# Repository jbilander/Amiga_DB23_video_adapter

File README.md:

# Amiga DB23 Video Adapter

## Overview

The Amiga DB23 Video Adapter is a small plug-mounted PCB that fits directly onto the Amiga's 
DB23 video port. It is primarily used to build Amiga video cables — either a SCART (RGBS) or 
VGA (RGBHV) cable — while also buffering and filtering the Amiga's analog video signals for 
use with modern displays. Optionally, it allows switching between true PAL and NTSC clock 
frequencies without rebooting or using software.

***

***

<br />

***

### Video Signal Conditioning (Rev 1B)

- **HSync and VSync** are passed through a dual non-inverting Schmitt-trigger buffer (U1) to 
  reduce jitter and noise on the sync lines.
- **RGB signals** are routed through a THS7374 4-channel video amplifier (U3) with its 
  low-pass filter enabled. This effectively removes the horizontal banding and "jailbar" 
  interference patterns commonly seen when connecting an Amiga's 15 kHz signal to LCD displays.
  > ⚠️ A 15 kHz-capable display is required. See [15khz.wikidot.com](http://15khz.wikidot.com/) 
  > for compatible monitors.

### PAL/NTSC Clock Switching (Optional)

When a crystal oscillator (Y1) is populated, the adapter can supply an external pixel clock 
to the Amiga's Agnus/Alice chip, allowing the machine to be switched between PAL and NTSC 
video modes. The slide switch (SW1) enables or disables the `/XCLKEN` signal — when asserted, 
this tells Agnus/Alice to use the external clock from the adapter instead of the onboard 
motherboard oscillator.

The switch itself is hardware-debounced using a resistor-capacitor (RC) circuit combined with 
the hysteresis of a dual-inverting Schmitt-trigger IC (U2), ensuring clean, glitch-free 
switching.

Two solder pads (`XCLKEN` and `/XCLKEN`) are provided on the PCB. An optional jumper wire 
can be soldered from one of these pads back to pin 41 of a switchable Agnus chip 
(or JP4 on the A500 Rev. 6A board), so that the switch on the adapter controls both the 
external clock enable and the Agnus clock selection simultaneously.

> ⚠️ **Before attempting this mod**, verify that your Agnus revision supports hardware 
> PAL/NTSC switching, and confirm that JP4 is not already bridged to GND. 
> All ECS Agnus chips can be switched in **software** if the hardware pin is not available — 
> use the Early Startup Menu (hold both mouse buttons at reset) on KS 3.0+, or a tool 
> such as [Degrader](https://aminet.net/package/util/boot/Degrader).

#### Choosing the correct crystal and solder pad

Install a crystal **opposite** to the one already on your Amiga's motherboard:

| Motherboard oscillator | Install crystal | Solder jumper wire to pad |
|------------------------|-----------------|---------------------------|
| PAL (28.37516 MHz)     | NTSC (28.63636 MHz) | `XCLKEN` |
| NTSC (28.63636 MHz)    | PAL (28.37516 MHz)  | `/XCLKEN` |

> The jumper wire is entirely optional. Without it you can still enable/disable the external 
> clock via SW1, and switch the Agnus video mode independently through software or the 
> Early Startup Menu.

---

## Why use this adapter with XCLK?

You don't have to — but being able to switch between true native PAL and true native NTSC on 
the same machine is a very compelling feature. It gives you:

- ✅ Correct **aspect ratio** for game graphics designed for a specific video standard
- ✅ Correct **sound playback speed** (PAL/NTSC run at different clock rates)
- ✅ Correct **gameplay speed** and smooth scrolling in both PAL 50 Hz and NTSC 60 Hz

For example, compare the screenshots below from *Defender of the Crown*, with its stunning 
artwork by artist **Jim Sachs**. The game was designed for NTSC and looks significantly better 
in NTSC mode (bottom row) — in PAL mode (top row) everything appears vertically squashed.

<br />

**PAL (top) vs NTSC (bottom):**

***

## Usage Scenarios

### 1 — Amiga DB23 to SCART (RGBS)
Build a cable carrying RGB + Composite Sync (CSync) to a SCART-equipped display.  
U1 and C3 are **not required** in this configuration.  
Y1 can optionally be populated for PAL/NTSC switching as described above.

### 2 — Amiga DB23 to VGA (RGBHV)
Build a cable carrying RGB + separate HSync/VSync to a VGA monitor.  
Requires a [15 kHz-compatible monitor](http://15khz.wikidot.com/).  
U1 and C3 **are required** in this configuration.  
Y1 can optionally be populated for PAL/NTSC switching as described above.

### 3 — Plug only, no cable (clock switching only)
Populate Y1 and the XCLK circuitry, but attach no output cable. Useful if you are already 
using an RGBtoHDMI or similar device for display output but want to retain hardware 
PAL/NTSC switching via the adapter's switch.

***

## Bill of Materials (Rev 1B and 1C)

**J1, U3 and RN1 are required for both SCART and VGA builds.**

| Reference | Qty | Value | Description | Package | Mouser / Notes |
|-----------|-----|-------|-------------|---------|----------------|
| J1 | 1 | DB23 Female | DB-23 female connector (Amiga video port) | DB-23 | [Aliexpress DB23 Female](https://www.aliexpress.com/item/1005004634222021.html) |
| U1 | 1 | 74HCT2G17 | Dual non-inverting Schmitt-trigger buffer — **VGA only** | TSOP-6 | [771-HCT2G17GV125](https://www.mouser.com/ProductDetail/771-HCT2G17GV125) |
| U2 | 1 | 74HCT2G14 | Dual inverting Schmitt-trigger buffer (SW1 debounce) — **XCLK optional** | TSOP-6 | [771-HCT2G14GV125](https://www.mouser.com/ProductDetail/771-HCT2G14GV125) |
| U3 | 1 | THS7374IPWR | 4-channel video amplifier with low-pass filter | TSSOP-14 | [595-THS7374IPWR](https://www.mouser.com/ProductDetail/595-THS7374IPWR) |
| U4 | 1 | 74LVC1GX04 | Crystal clock buffer — **XCLK optional** | TSOP-6 | [771-LVC1GX04GV125](https://www.mouser.com/ProductDetail/771-LVC1GX04GV125) |
| Y1 | 1 | 28.37516 MHz (PAL) or 28.63636 MHz (NTSC) | Crystal oscillator, CL=16pF — **XCLK optional** | 3.2 x 2.5 mm | e.g. ABM8-28.375MHZ-B2-T (PAL) or ECS-286.3-18-33-JEM-TR (NTSC) |
| RN1 | 1 | 75Ω | Resistor network, 4× 75Ω isolated (CAT16-75R0F4LF) | 1206 | [CAT16-75R0F4LF](https://www.mouser.com/ProductDetail/652-CAT16-75R0F4LF) |
| SW1 | 1 | SW_SPDT | Slide switch, enables/disables `/XCLKEN` (external clock to Agnus/Alice). Recommended: SS12D00 3-pin 1P2T, pin pitch 2.5 mm, handle length 5 mm — **XCLK optional** | | e.g. [AliExpress SS12D00](https://www.aliexpress.com/item/1005008330569768.html) |
| R1 | 1 | 100Ω | **Optional** — CCK clock termination. Populate only if experiencing clock interference noise. See [vidmod fix](http://www.l8r.net/technical/wblock/a4000hard/vidmod.html) | 1206 | |
| R2 | 1 | 75Ω | RGB mode autoselect — **SCART only** (drives SCART pin 16 high for RGB mode) | 1206 | |
| R3 | 1 | 1kΩ | AV mode autoselect — **SCART only** (drives SCART pin 8 high at 9.5–12V so TV automatically switches to SCART input) | 1206 | |
| R4 | 1 | 150Ω | Damping resistor XCLK-line — **XCLK optional** | 1206 | |
| R5 | 1 | 330Ω | CSync resistor — **SCART only** | 0805 | |
| R6, R7, R8 | 3 | 75Ω | Video termination resistor | 0603 | |
| R9, R10 | 2 | 10kΩ | Resistor (SW1 RC debounce) — **XCLK optional** | 0805 | |
| R11 | 1 | 1kΩ | Resistor — **XCLK optional** | 0603 | |
| R12 | 1 | 2.2MΩ | Resistor — **XCLK optional** | 0603 | |
| C1, C2 | 2 | 100nF | Decoupling capacitor | 0805 | (C2 is for SW1 RC debounce)|
| C3 | 1 | 100nF | Decoupling capacitor — **VGA only** | 0603 | |
| C4, C5 | 2 | 100nF | Decoupling capacitor — **XCLK optional** | 0603 | |
| C6, C7 | 2 | 32pF | Crystal load capacitor (06031A320FAT2A) — **XCLK optional** | 0603 | [581-06031A320FAT2A](https://www.mouser.com/ProductDetail/581-06031A320FAT2A) |

### Partial BOM by build type

| Component | Mandatory (both) | SCART only | VGA only | XCLK optional |
|-----------|:---:|:---:|:---:|:---:|
| J1, U3, RN1 | ✅ | | | |
| C1, R6, R7, R8 | ✅ | | | |
| R2, R3, R5 | | ✅ | | |
| U1, C3 | | | ✅ | |
| U2, U4, Y1, SW1 | | | | ✅ |
| C2, C4, C5, C6, C7 | | | | ✅ |
| R4, R9, R10, R11, R12 | | | | ✅ |
| R1 | optional | | | |

### SCART cable wiring reference

| Signal | Resistor | Value | SCART pin | Notes |
|--------|----------|-------|-----------|-------|
| CSync  | R5 | 330Ω | Pin 20 | Composite sync / composite video in, 1V incl. sync |
| +5V    | R2 | 75Ω  | Pin 16 | RGB select: High (1–3V) = RGB mode, Low (0–0.4V) = Composite |
| +12V   | R3 | 1kΩ  | Pin 8  | AV autoswitch: High (9.5–12V) = AV mode, Low (0–2V) = TV mode |

### VGA cable reference

U1 (74HCT2G17) buffers HSync and VSync. Datasheet: [74HC/HCT2G17](https://assets.nexperia.com/documents/data-sheet/74HC_HCT2G17.pdf)

---

## How to build Rev 1B

The following step-by-step guide documents a VGA (RGBHV) cable build using a cheap 
thin VGA cable as the source, which works very well since these cables already contain 
individually shielded wires inside.

### Step 1 — Prepare the DB23 connector

Start by gently prying the solder lug pins outward slightly on the DB23 connector so 
that they can wrap around the standard 1.6 mm PCB thickness. The back of a pair of 
tweezers works well for this — just enough to open them up without bending them too far.

### Step 2 — Fit the PCB into the connector

Carefully sandwich the PCB between the solder cups of the connector, making sure the 
alignment is correct. The fit is very tight — press the PCB in by hand as far as it 
will go. At this stage there will still be a small gap visible between the blue plastic 
back of the connector and the PCB edge; this is expected.

### Step 3 — Press the PCB fully home in a vise

Place the PCB and connector assembly into a bench vise as shown, then slowly tighten 
the vise to press the PCB all the way flush against the plastic back of the connector.

### Step 4 — Test fit in the plastic shell

Test that the assembly fits inside the plastic shell and clears the screw terminal posts.

> **Note on shell compatibility:**
> - **Older DB23 shells** have approximately 21.5 mm clearance between the screw terminal 
>   posts — Rev 1B (20.6 mm wide) fits these without any modification.
> - **Newer shells** (available from [AliExpress](https://www.aliexpress.com/item/1005004634222021.html)) 
>   have only 20 mm spacing, which means Rev 1B overlaps the posts by about 0.6 mm and 
>   the two shell halves will not close without a slight carve or filing of the plastic posts.
> - **Rev 1C** has been narrowed to 19.8 mm and fits the new shells without any modification. 
>   Rev 1B and Rev 1C are otherwise electrically identical — the BOM and schematic are the same.

In pic9, the right side shows a fully soldered connector test-fitted in an older shell 
where it clears the posts cleanly. On the left you can see a bare PCB test-fitted in the 
newer style shell, where the slight overlap on the posts is visible.

Once you have confirmed the fit, solder all the connector solder cups on both sides of 
the PCB and connector.

### Step 5 — Solder the SMD components

With the connector soldered, proceed to populate and solder the SMD components on the 
PCB. If you are fitting the optional crystal oscillator (Y1) for XCLK switching, it is 
recommended to reflow it first with a hot air rework station before populating nearby 
smaller components that could otherwise be displaced by the airflow. All other SMD 
components can be soldered with a regular soldering iron.

Leave the through-hole slide switch (SW1) until last — it is easier to solder everything 
else first without the switch body in the way.

> **Tip on cable shielding:** It is good practice to solder the cable's outer shielding 
> braid to the DB23 connector's metal shell. The Amiga's DB23 shell is connected to GND 
> on the motherboard, so having the shield connected here means GND will make contact 
> first if the cable is ever hot-plugged, protecting the circuitry. A high-powered 
> soldering iron or desoldering gun (such as the ZD-915) with sufficient thermal mass 
> is recommended for this step. Pre-crimping a Dupont male pin onto the bundled shielding 
> wire makes it easier to tin and solder to the shell.

### Step 6 — Modify the shell for the cable strain relief

To fit the metal cable strain relief inside the shell, the two small inner plastic walls 
nearest the cable exit hole need to be removed — they are the ones that interfere with 
the strain relief clamp. Use a pair of electronics pliers or flush cutters to snip them 
off as close to the side wall and floor of the shell as possible. Be careful to only 
remove the two pieces immediately next to the exit hole, not the similar supports further 
inside that the PCB rests on.

### Step 7 — Modify the strain relief to fit

The standard metal cable strain relief may need a small amount of filing to fit 
comfortably inside the shell. The standard M3 screws supplied with the strain relief 
may also need to be swapped for M3 screws with a lower-profile head. Once modified, 
the strain relief fits neatly wedged between the back edge of the PCB and the rear 
wall of the shell. Alternatively, a custom strain relief could be 3D printed in plastic 
to avoid the need for any hand filing.

### Step 8 — Drill the switch hole

One half of the plastic shell needs a hole drilled for the SW1 switch handle to protrude 
through. Mark the centre point with a sharp tweezer or scribe — it sits midway between 
the two screw holes, and midway between the recessed label area and the thumb-grip 
grooves on the shell.

Start with a 1 mm drill bit turned carefully by hand to establish a centred pilot hole, 
then step up through 2 mm, 4 mm, and finally 6 mm using a power drill. A 6 mm diameter 
hole gives the switch handle enough room to travel freely between both positions without 
touching the sides.

### Step 9 — Test fit the switch

Test fit the shell halves and confirm that the switch handle protrudes a few millimetres 
through the hole and can be toggled comfortably between both positions by hand.

### Step 10 — Solder the cable wires

Solder the cable wires to the solder pads on the PCB:

- **Underside (pic14):** All GND wires are soldered here. In this VGA build the 5V and 
  12V pads are unused.
- **Front side (pic15):** The analogue Red, Green and Blue signal wires are soldered to 
  their respective pads, along with HSync (grey wire) and VSync (white wire).

### Step 11 — The finished cable

The completed Amiga DB23 to VGA cable. The cable used here is a standard thin VGA cable, 
which despite being inexpensive is an excellent choice as the individual signal wires 
inside are already shielded.

---

## How to build a SCART (RGBS) cable — Rev 1B

The following documents a SCART cable build. This build also includes audio by extending 
wires from a separate RCA cable into the SCART cable, giving you a complete audio/video 
solution in a single plug.

### Step 1 — Solder the top side signal wires

The top side of the PCB with all signal wires soldered. The Red, Green and Blue wires 
connect to the R, G and B pads respectively, and the yellow wire carries CSync to the S 
pad. The audio channels are extended from a separate RCA cable — Red (Right channel) and 
black-to-white (Left channel) — running alongside the video wires into the SCART cable. 
The two audio GND return wires are bundled together and soldered to the GND pad on the 
side of the PCB.

### Step 2 — Crimp and sleeve the audio wire extensions

The audio wire extensions were first crimped and then soldered for a solid mechanical and 
electrical connection. Heat shrink tubing was applied over each joint and carefully 
shrunk at 150°C using a hot air station, giving a clean and well-insulated result as 
seen in pic25.

### Step 3 — Solder the underside wires

The underside of the PCB with everything soldered except the shield ground. Visible here 
are the 5V and 12V wires, the GND wires (main GND plus three RGB return GND wires), and 
the optional fly-lead wire to the `XCLKEN` pad for hardware PAL/NTSC switching via a 
jumper wire to Agnus.

### Step 4 — Solder the cable shielding to the D-Sub metal shell

The cable's outer shielding braid is soldered directly to the DB23 D-Sub metal shell. 
This grounds the shielding and is particularly important for hot-plugging — with the 
shield connected to the Amiga's motherboard GND via the DB23 shell, GND makes contact 
first when the plug is inserted, protecting the circuitry from damage.

### Step 5 — Fit the cable into the shell with strain relief

The fully built cable assembly fitted inside the DB23 shell with the strain relief in 
place. The strain relief needed filing down to fit comfortably in the somewhat cramped 
interior, as described in the VGA build guide above.

### Step 6 — The completed SCART plug

The completed plug with the 5 mm hole drilled for the switch handle, which protrudes 
cleanly and travels freely between both positions without obstruction.

### Step 7 — The result: sharp picture quality via SCART

The Kickstart 1.3 boot screen displayed via the SCART cable on a TV. The picture quality 
is excellent — sharp, well-saturated RGB with no banding or jailbar artefacts. Almost 
HDMI-like quality from a 15 kHz analog signal.

### Step 8 — The cable connected to the Amiga 500

A close-up of the completed SCART cable plugged into the Amiga 500, with the separate 
RCA audio cable also connected.

---

## Rev 1B in action

### The cable connected to an Amiga 500+

The DB23 end of the completed VGA cable plugged into the Amiga 500+. The switch handle 
is clearly visible on the side of the shell and can be toggled by hand to switch between 
PAL and NTSC clock modes.

### XCLK signal verified on the oscilloscope

Oscilloscope capture of the XCLK signal measured at pin 1 on the back of the Amiga DB23 
male connector. The adapter produces a clean 28.64 MHz clock signal as expected for NTSC 
operation.

### Working on the BenQ BL912 — PAL and NTSC

The BenQ BL912 is an excellent 15 kHz-capable monitor for use with the Amiga. The monitor 
OSD System → Information screen confirms the signal being received directly from the VGA 
cable via D-Sub input.

**PAL mode** — the monitor information screen shows the Amiga running at 576i @ 50 Hz 
over D-Sub.

**NTSC mode** — after flipping the switch on the adapter, the monitor information screen 
now shows 480i @ 59 Hz. The Kickstart 3.1 screen fills the display correctly with the 
proper NTSC aspect ratio.

### Working on the AOC 24E1Q — PAL and NTSC

**PAL mode** on the AOC 24E1Q displayed in 4:3 mode.

**NTSC mode** on the AOC 24E1Q displayed in 4:3 mode.

### SCART cable on a Panasonic Plasma — PAL and NTSC

The SCART cable tested on a Panasonic plasma TV with the Amiga 500. The picture quality 
is outstanding — sharp, clean RGB with no banding or jailbar artefacts, almost HDMI-like 
in quality.

The SCART cable running from the Amiga 500 to the Panasonic plasma, with the separate 
RCA audio cable also connected.

**PAL mode** — SysInfo running on the Panasonic plasma via SCART. The TV OSD confirms 
the AV colour system. The Amiga is running from the internal 28.37516 MHz PAL oscillator 
on the motherboard, which is why the CPU speed is displayed as 7.09 MHz.

**NTSC mode** — SysInfo after flipping the switch to engage the external XCLK 28.63636 
MHz oscillator circuit on the adapter. The CPU speed now reads 7.16 MHz confirming the 
machine is running on the NTSC clock. Both PAL and NTSC modes produce an excellent sharp 
picture via SCART.

Workbench 3.1.4 running in PAL mode on the Panasonic plasma via SCART. The picture 
quality speaks for itself.

---

## Optional mod: A500 Rev 6A hardware PAL/NTSC switching without a fly-lead

If you have an Amiga 500 Rev 6A motherboard, there is a neat alternative to running a 
separate fly-lead wire from the `XCLKEN` pad on the adapter back to Agnus pin 41. Instead 
of a wire, a single **1kΩ 1206 resistor** can be bodged directly between the `JP5C` pad 
and `JP4` pad 1 on the motherboard, connecting `_XCLKEN` to the Agnus PAL/NTSC pin 
(pin 41) via the existing JP4 jumper area.

> ⚠️ This mod assumes you have already **cut the trace between JP4 pad 1 and pad 2** 
> (which bridges pin 41 to GND on a standard PAL machine). Verify this cut with a 
> multimeter before proceeding — pad 1 must have no continuity to GND. Also confirm that 
> your Agnus revision supports hardware PAL/NTSC switching before attempting this mod.

The schematic excerpt below shows where the resistor connects:

The `_XCLKEN` signal (from JP5C) is connected through the 1kΩ resistor to JP4 pad 1, 
which leads to Agnus pin 41 (`_NTSC/PAL`). When the switch on the adapter asserts 
`_XCLKEN`, Agnus is simultaneously told to switch clock source, all controlled from the 
single switch on the DB23 plug — no separate fly-lead wire needed.

A 1206 1kΩ resistor bodged between the JP5C and JP4 pad 1 on the A500 Rev 6A 
motherboard. The 1206 package is convenient here as its footprint spans the gap between 
the two pads neatly.

---

***
***
***

### OLD rev 1A:
***

<br />

***

The HSync and VSync lines are buffered via a dual non-inverting Schmitt-trigger IC to reduce jitter and noise. The PAL/NTSC switch has a simple resistor-capacitor (RC) debounce circuit using the hysteresis in a dual-inverting Schmitt-trigger IC for proper debounce in hardware. This IC also controls the enabling (OE-pin) of the crystal oscillator as well as asserting the /XCLKEN line (pin 2). A solderpad with a jumper-pin exists for connecting a jumper-wire back to a switchable Agnus (Not all Agnuses are switchable) on pin 41 (or JP4 on A500 Rev. 6A), this is completely optional, check your Agnus version before trying such a mod and that JP4 isn't bridged to GND. All ECS Agnuses can be switched in Software should your Agnus not have the PAL/NTSC pin. KS 3.0 and above lets you switch in early startup menu that you can access by holding down the two mouse buttons right after resetting the machine.

***

***

With this adapter you can:

    1. Make an Amiga DB23 to SCART RGBS (RGB with CSync) cable, 
       and optionally populate X1 with either a 28.63636 MHz (NTSC) 
       or 28.37516 MHz (PAL) oscillator, obviously you'll choose a crystal here 
       opposite to what your machine has on the motherboard.

    or

    2. Make an Amiga DB23 to VGA RGBHV (RGB with separate HSync, VSync) cable 
       (This requires a 15 kHz compatible monitor http://15khz.wikidot.com/ ), 
       and optionally populate X1 with either a 28.63636 MHz (NTSC) 
       or 28.37516 MHz (PAL) oscillator, obviously you'll choose a crystal here 
       opposite to what your machine has on the motherboard.

    or

    3. Make a Plug-only with no cable and populate X1 with either a 28.63636 MHz (NTSC) 
       or 28.37516 MHz (PAL) oscillator, obviously you'll choose a crystal here 
       opposite to what your machine has on the motherboard. I assume you're using RGB2HDMI 
       or similar for hooking up your display but still want to be able to switch between true 
       PAL/NTSC by feeding XCLK to the machine.

***

If you use jumper-wire from JP1-pin then you bridge it either with the left pad or the right pad depending on your setup:

    1. Motherboard has PAL oscillator and Adapter has NTSC oscillator = bridge JP1-pin with XCLKEN-pad
    2. Motherboard has NTSC oscillator and Adapter has PAL oscillator = bridge JP1-pin with OE-pad

Please note, using a jumper-wire is completely optional, You can switch ECS Agnus in Early Startup menu or with software such as Degrader and then ju only switch the external XLCK-crystal enable or disable via the switch on the cable plug. However it can be more convenient to have both tasks controlled from one single switch, hence connecting a jumper-wire.

***

BOM SCART
---------
PART  | Value   | Description
----- | ------- | -------
R1    | 330 Ohm | 0805 &nbsp;&nbsp;&nbsp;(CSync), to Pin 20 of SCART, (Comp Video In, 1V including sync)
R2    | 75 Ohm  | 1206 &nbsp;&nbsp;&nbsp;(+5V), to Pin 16 of SCART, High (1-3V) RGB, Low (0-0.4V) Composite
R3    | 1k Ohm  | 1206 &nbsp;&nbsp;&nbsp;(+12V), to Pin 8 of SCART, Autoselect switch: High (9.5-12V) AVmode, Low (0-2V) TVmode

I used the Resistor-values following Stedy's guide here: <br /><br />
The Ultimate SCART cable <br />
http://ianstedman.co.uk/amiga-scart-guide/

BOM VGA
-------
PART  | Value     | Description
----- | --------- | -------
U1    | 74HCT2G17 | TSOP-6 (Dual non-inverting Schmitt trigger), (HSync, VSync) <br />https://assets.nexperia.com/documents/data-sheet/74HC_HCT2G17.pdf
C2    | 0.1 uF    | 0805

BOM XCLK
--------
PART  | Value      | Description
--------- | ---------- | -------
R4        | 10k Ohm    | 0805
R5        | 10k Ohm    | 0805
C1        | 0.1 uF     | 0805
C3        | 0.1 uF     | 0805
C4        | 0.1 uF     | 0805
U2        | 74HCT2G14  | TSOP-6 (Dual inverting Schmitt trigger) <br />https://assets.nexperia.com/documents/data-sheet/74HC_HCT2G14.pdf
X1 (PAL)  | 28.375 MHz  | Standard Clock Oscillator 5V (7.5 mm x 5 mm)<br />LFSPXO014117Bulk<br />https://eu.mouser.com/datasheet/2/741/LFSPXO014117Bulk-983232.pdf <br /> 91 pcs In Stock at the time of writing
X1 (NTSC) | 28.6363 MHz | XO (Standard) CMOS Oscillator 5V (7 mm x 5 mm)<br />K50-HC0CSE28.6363MR<br />https://media.digikey.com/pdf/Data%20Sheets/AVX%20PDFs/K50-HC%20Series%20Oscillators.pdf<br />895 pcs In Stock at the time of writing
JP1       | | Solder Jumper with pin for a flylead back to switchable Agnus pin 41 (or its pad on motherboard, e.g. JP4 on A500 Rev.6A)
SW1       | Handle length: 3mm-6mm| On-Off mini slide switch SS12D00 3pin 1P2T 2 Position toggle switch

***

## Howto modify a vga-cable and use with this adapter

First do some soldering, standard stuff nothing special:

***

Ok good, now the switch, solder it on and make a hole in the plastic hood (several small drill holes will do, or one 5 mm bulls-eye drill hole.):
<br />

***

Now time to butcher one side of the vga cable:

<br />

<br />

***

Now, first thing first, put a larger shrink tube around the cable (blue in picture) and then start cutting and stripping wires, you can beep out which one is which. In this cable all the individually shielded wires were RGBHV. Wire together the cable shielding like in picture below and use a shrink tube around. Pic below says it all:

***
Optional flylead:
<br /><br />
Now add a jumper wire with a right angled pin (crimped or soldered to the wire) and solder it onto JP1 bridging it with either of the pads (which one depends on your setup).

***
Now, solder the shielding to the metal casing, I first tried without crimping a pin on there but couldn't get a good joint. I used my desolder gun 80W giving enough juice/heat to be able to solder this one finally:

<br />

Ok, now heat the blue shrink tube and fit the cable stop, don't tighten too hard.

<br />

I did some testing that the switch works, and also I beeped out the cable verifying no shorts exists before trying it:

***
Installing jumper wire in A500 Rev 6A:
<br />

I ran the jumper wire through an existing hole in the Amiga 500 case/motherboard, then just soldered it onto JP4 pad next to Agnus verifying no continuity to GND-pad:

***

All done! We can now switch between true PAL/NTSC and get correct display resolution, yay!

***

We can even switch during run-time thanks to the proper debounce circuit in hardware, but I think it's best to power off the Amiga, do the switching, and then power on again.

Short video-clip below showing hot-switching, don't try this at home folks ;)

https://imgur.com/iBLLAlT

Here a comparison between PAL vs NTSC on WB 3.1.4 on a A1200 and a Benq BL912 tweaked with pixelclock setting around 90 and some overscan, very nice picture quality I must say:

<br />
<br />
It is very important to adjust the pixelclock on the Benq monitor to get rid of those vertical jailbars, otherwise it will look like this:
<br />
<br />

<br />
<br />
If you ever wondered how one of those moulded vga plugs looks like inside, this is it:
<br />
<br />

***

## Howto solder a SCART-cable (RGBS) with this adapter.

<br />

<br />
<br />
First the resistors R1-R3 and then the oscillator with its decoupling cap:
<br />
<br />

***

I'm using a cut-down DB25 to DB23 here and because of this I didn't solder the PCB flush against the connector as you would normally do, this is to make the PCB fit in the slighly larger plastic shroud of the DB25. Solder the mini-slide switch as the last step after the 23-pins for easier soldering:

<br />
<br />

Drill out a hole for the switch 5 mm or similar and if needed cut some plastic from the shroud to clear the oscillator:

<br />

<br />

<br />

***

Now, add shrinktubes on the main cable and for the shielding and the L and R audio wires...then solder all the wires to the PCB and crimp the audio wires together, audio GND can be wired together and soldered to the GND pad(s) of the PCB:
<br />
<br />

<br />
<br />
Add the jumper-wire-pin and solder the slide switch and the shielding last (I use my desolder gun 80W to be able to solder the shielding):
<br />
<br />

<br />
<br />
Ok all done with the d-sub connector...
<br />
<br />

<br />
<br />
...now the Scart-plug, this is straight forward soldering, nothing special, I use a stick from a q-tip to separate the pin rows to not risk any shorts. I find it holds the pins better in position too.
<br />
<br />

***

<br />
All done!
<br />
<br />
Here another SCART-cable I made, this time with a real DB23 plug:
<br />
<br />

***
As a last step, don't forget to select Game Mode and the correct AV-mode on your TV.
<br />
<br />

<br />
<br />
Game On!
<br />
<br />
Happy Hackin´

***

<br />
<br />

[![CC BY-SA 4.0][cc-by-sa-shield]][cc-by-sa]

This work is licensed under a
[Creative Commons Attribution-ShareAlike 4.0 International License][cc-by-sa].

[![CC BY-SA 4.0][cc-by-sa-image]][cc-by-sa]

[cc-by-sa]: http://creativecommons.org/licenses/by-sa/4.0/
[cc-by-sa-image]: https://licensebuttons.net/l/by-sa/4.0/88x31.png
[cc-by-sa-shield]: https://img.shields.io/badge/License-CC%20BY--SA%204.0-lightgrey.svg

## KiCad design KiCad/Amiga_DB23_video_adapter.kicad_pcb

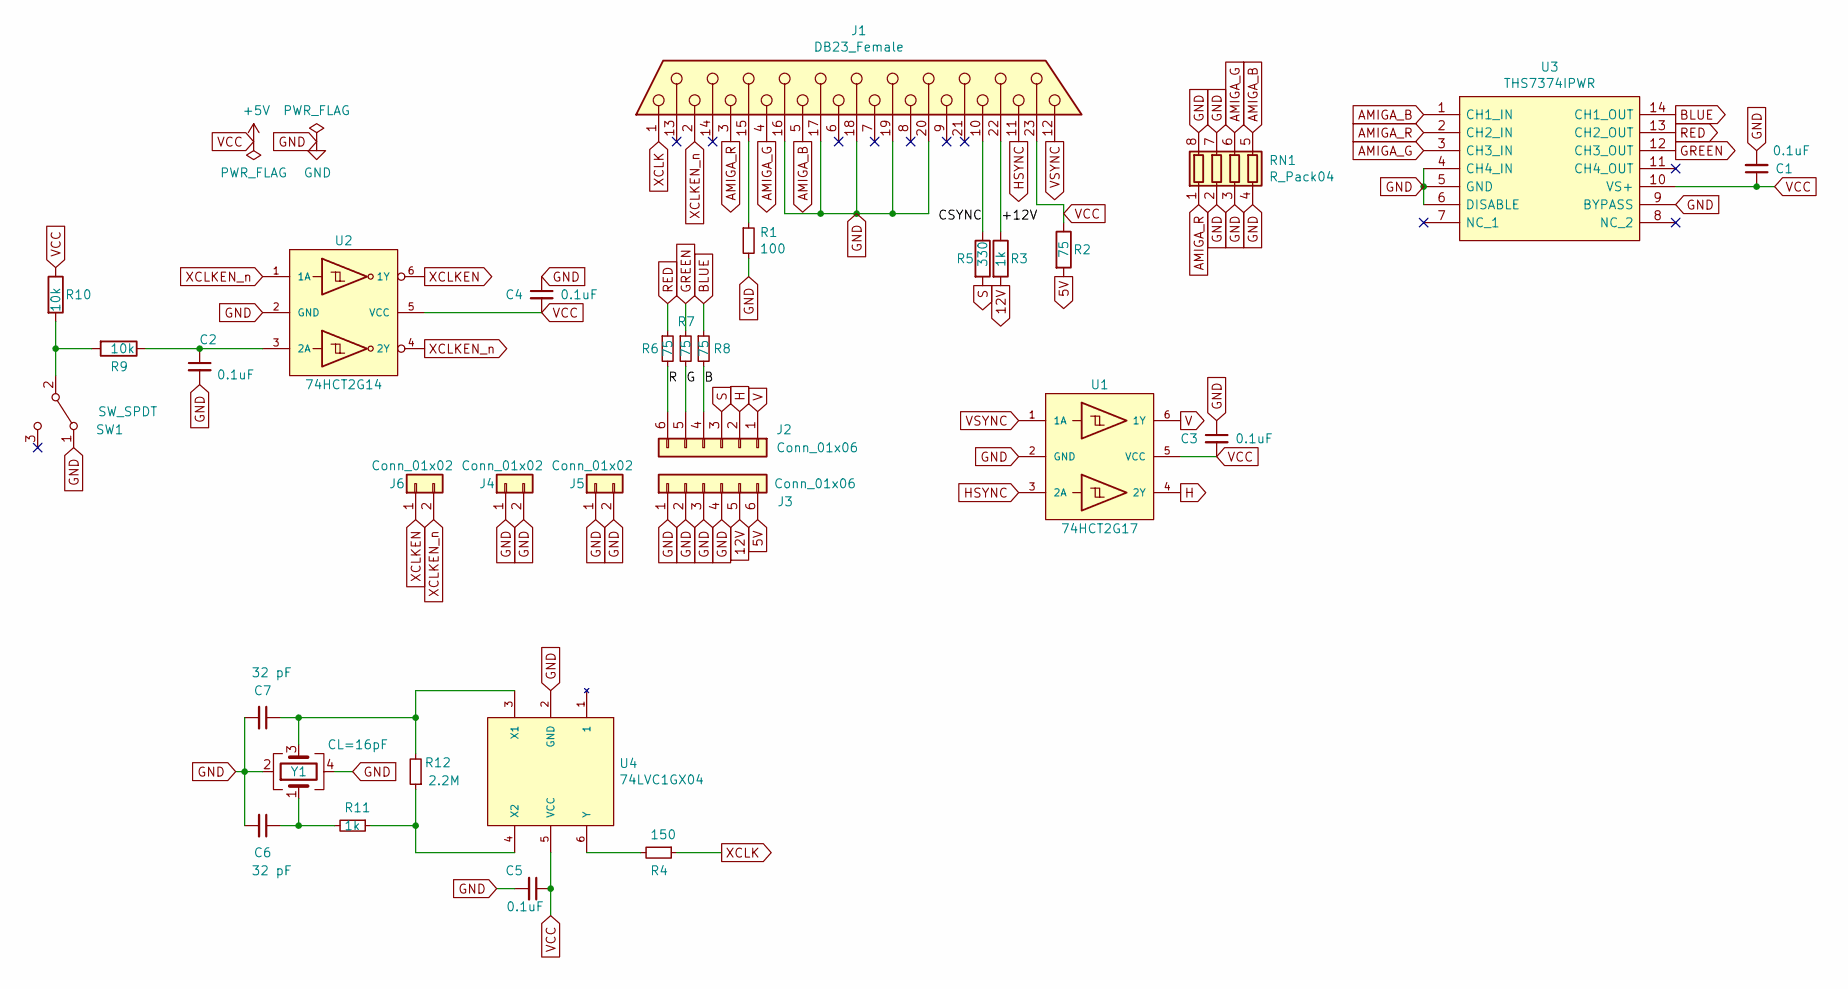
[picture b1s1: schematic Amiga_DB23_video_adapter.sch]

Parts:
C1, C2: 0.1uF; C_0805_2012Metric_Pad1.15x1.40mm_HandSolder
C3, C4, C5: 0.1uF; C_0603_1608Metric_Pad1.08x0.95mm_HandSolder
C6, C7: 32 pF; C_0603_1608Metric_Pad1.08x0.95mm_HandSolder
J1: DB23_Female; DSUB-23_Female_EdgeMount_P2.77mm
J2, J3: Conn_01x06; PinHeader_1x06_P2.00mm_Vertical
J4, J5, J6: Conn_01x02; PinHeader_1x02_P2.00mm_Vertical
R1: 100; R_1206_3216Metric_Pad1.30x1.75mm_HandSolder
R2: 75; R_1206_3216Metric_Pad1.42x1.75mm_HandSolder
R3: 1k; R_1206_3216Metric_Pad1.42x1.75mm_HandSolder
R4: 150; R_1206_3216Metric_Pad1.30x1.75mm_HandSolder
R5: 330; R_0805_2012Metric_Pad1.15x1.40mm_HandSolder
R6, R7, R8: 75; R_0603_1608Metric_Pad0.98x0.95mm_HandSolder
R9, R10: 10k; R_0805_2012Metric_Pad1.15x1.40mm_HandSolder
R11: 1k; R_0603_1608Metric_Pad0.98x0.95mm_HandSolder
R12: 2.2M; R_0603_1608Metric_Pad0.98x0.95mm_HandSolder
RN1: R_Pack04; RESCAF80P320X160X60-8N
SW1: SW_SPDT; PinHeader_1x03_P2.54mm_Vertical
U1: 74HCT2G17; TSOP-6_1.65x3.05mm_P0.95mm
U2: 74HCT2G14; TSOP-6_1.65x3.05mm_P0.95mm
U3: THS7374IPWR; TSSOP-14_4.4x5mm_P0.65mm
U4: 74LVC1GX04; TSOP-6_1.65x3.05mm_P0.95mm
Y1: CL=16pF; Crystal_SMD_SeikoEpson_FA238-4Pin_3.2x2.5mm

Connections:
5V: J3.6, R2.2
12V: J3.5, R3.2
/+12V: J1.22, R3.1
/B: J2.4, R8.2
/CSYNC: J1.10, R5.1
/G: J2.5, R7.2
/R: J2.6, R6.2
AMIGA_B: J1.5, RN1.5 (R4.2), U3.1 (CH1_IN)
AMIGA_G: J1.4, RN1.6 (R3.2), U3.3 (CH3_IN)
AMIGA_R: J1.3, RN1.1 (R1.1), U3.2 (CH2_IN)
BLUE: R8.1, U3.14 (CH1_OUT)
GND: C1.2, C2.2, C3.1, C4.1, C5.2, C6.2, C7.2, J1.16, J1.17, J1.18, J1.19, J1.20, J3.1, J3.2, J3.3, J3.4, J4.1, J4.2, J5.1, J5.2, R1.2, RN1.2 (R2.1), RN1.3 (R3.1), RN1.4 (R4.1), RN1.7 (R2.2), RN1.8 (R1.2), SW1.1 (A), U1.2 (GND), U2.2 (GND), U3.4 (CH4_IN), U3.5 (GND), U3.6 (DISABLE), U3.9 (BYPASS), U4.2 (GND), Y1.2, Y1.4
GREEN: R7.1, U3.12 (CH3_OUT)
H: J2.2, U1.4 (2Y)
HSYNC: J1.11, U1.3 (2A)
unnamed: C2.1, R9.1, U2.3 (2A)
unnamed: C6.1, R11.2, Y1.1
unnamed: C7.1, R12.2, U4.3 (X1), Y1.3
unnamed: J1.15, R1.1
unnamed: R4.2, U4.6 (Y)
unnamed: R9.2, R10.2, SW1.2 (B)
unnamed: R11.1, R12.1, U4.4 (X2)
RED: R6.1, U3.13 (CH2_OUT)
S: J2.3, R5.2
V: J2.1, U1.6 (1Y)
VCC: C1.1, C3.2, C4.2, C5.1, J1.23, R2.1, R10.1, U1.5 (VCC), U2.5 (VCC), U3.10 (VS+), U4.5 (VCC)
VSYNC: J1.12, U1.1 (1A)
XCLK: J1.1, R4.1
XCLKEN: J6.1, U2.6 (1Y)
XCLKEN_n: J1.2, J6.2, U2.1 (1A), U2.4 (2Y)

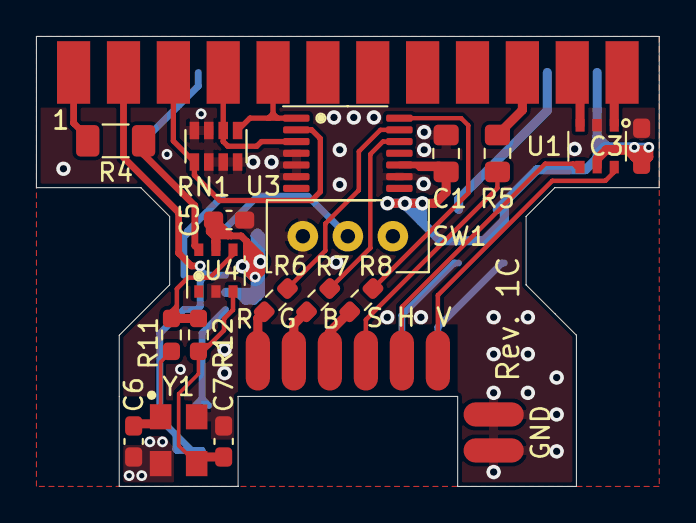
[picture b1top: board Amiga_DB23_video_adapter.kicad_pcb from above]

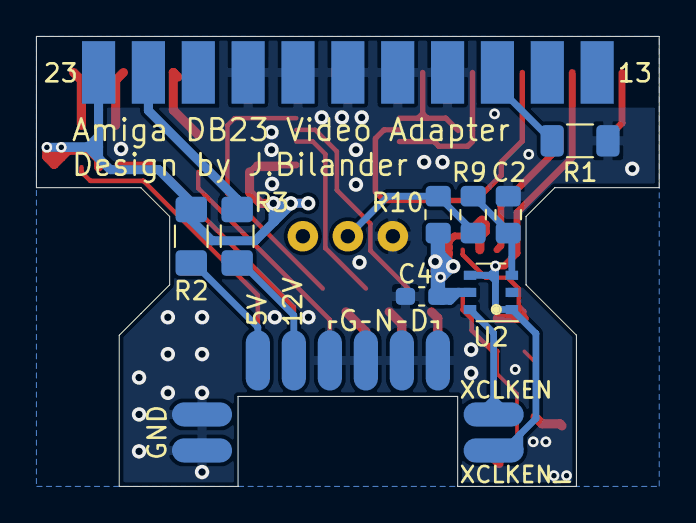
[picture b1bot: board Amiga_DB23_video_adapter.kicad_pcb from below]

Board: 4 copper layers, 34.6 x 25.0 mm, 32 parts (11 on the bottom side), 30 nets.

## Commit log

2021-04-14 added license file
2021-04-14 added pics
2021-04-22 added images
2021-04-22 added files
2021-04-22 renamed file
2021-08-18 deleted file
2026-03-08 Add footprint
2026-03-08 Add footprint folder
2026-03-12 Go to 4 layers
2026-03-12 Add THS7374IPWR and 74LVC1GX04 symbols
2026-03-12 Add new design based on a THS7374IPWR, 28M oscillator circuit, remove SolderJumper, complete re-design and re-route
2026-03-13 Add 3D model of resistor network
2026-03-13 Improve GND-stitching and fix silkscreen text and add new revision identifier
2026-03-13 Swap references C2,C3. Swap references C5,C7. Swap references R1,R9. Swap references R4,R12
2026-03-13 Swap references R5,R9. Swap references R10,R12
2026-03-13 Swap references R11,R12 and fix positioning of R10
2026-03-13 Update with new plot settings
2026-03-13 Add schematic pdf
2026-03-15 Add screenshots
2026-03-30 Small fix of physical size to better fit the plastic DB23 shell, bump to Rev 1C
2026-04-04 Add images
2026-04-04 Update README.md
    docs: update README for Rev 1B with build guide.
    - Add step-by-step Rev 1B build guide with photos (pic5–pic16) covering connector preparation, PCB fitting, shell modification, strain relief, switch hole drilling and cable wiring
2026-04-04 fix size of image
2026-04-05 docs: add Rev 1B in-action section with photos of cable connected to Amiga 500+
2026-05-08 docs: add SCART cable build guide with photos (pic25–pic32)
2026-05-09 docs: add Panasonic plasma SCART results and A500 Rev 6A resistor bodge mod

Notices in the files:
README.md:
CC BY-SA 4.0
This work is licensed under a
[Creative Commons Attribution-ShareAlike 4.0 International License][cc-by-sa].
